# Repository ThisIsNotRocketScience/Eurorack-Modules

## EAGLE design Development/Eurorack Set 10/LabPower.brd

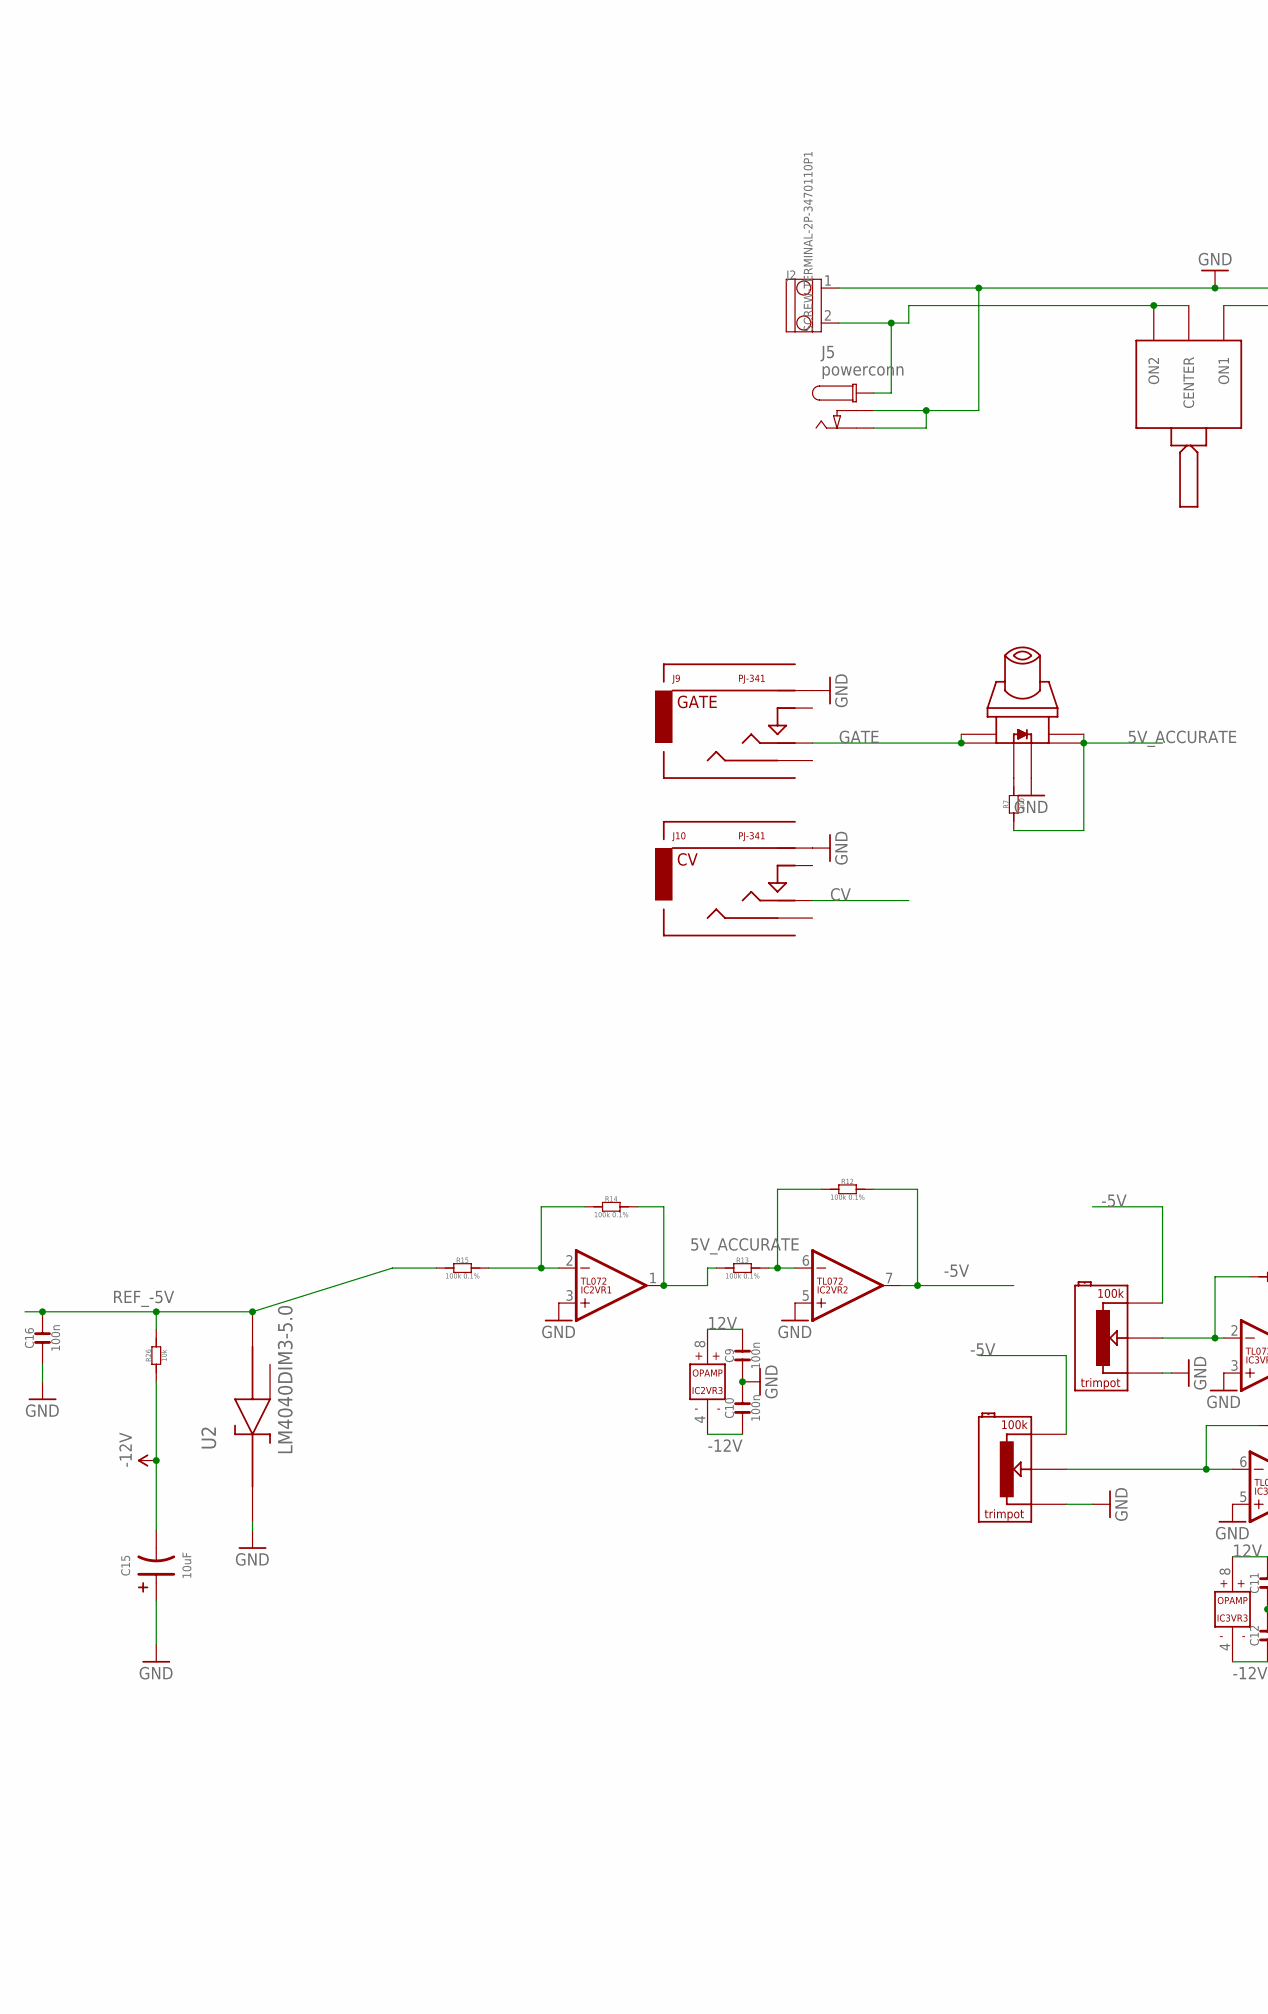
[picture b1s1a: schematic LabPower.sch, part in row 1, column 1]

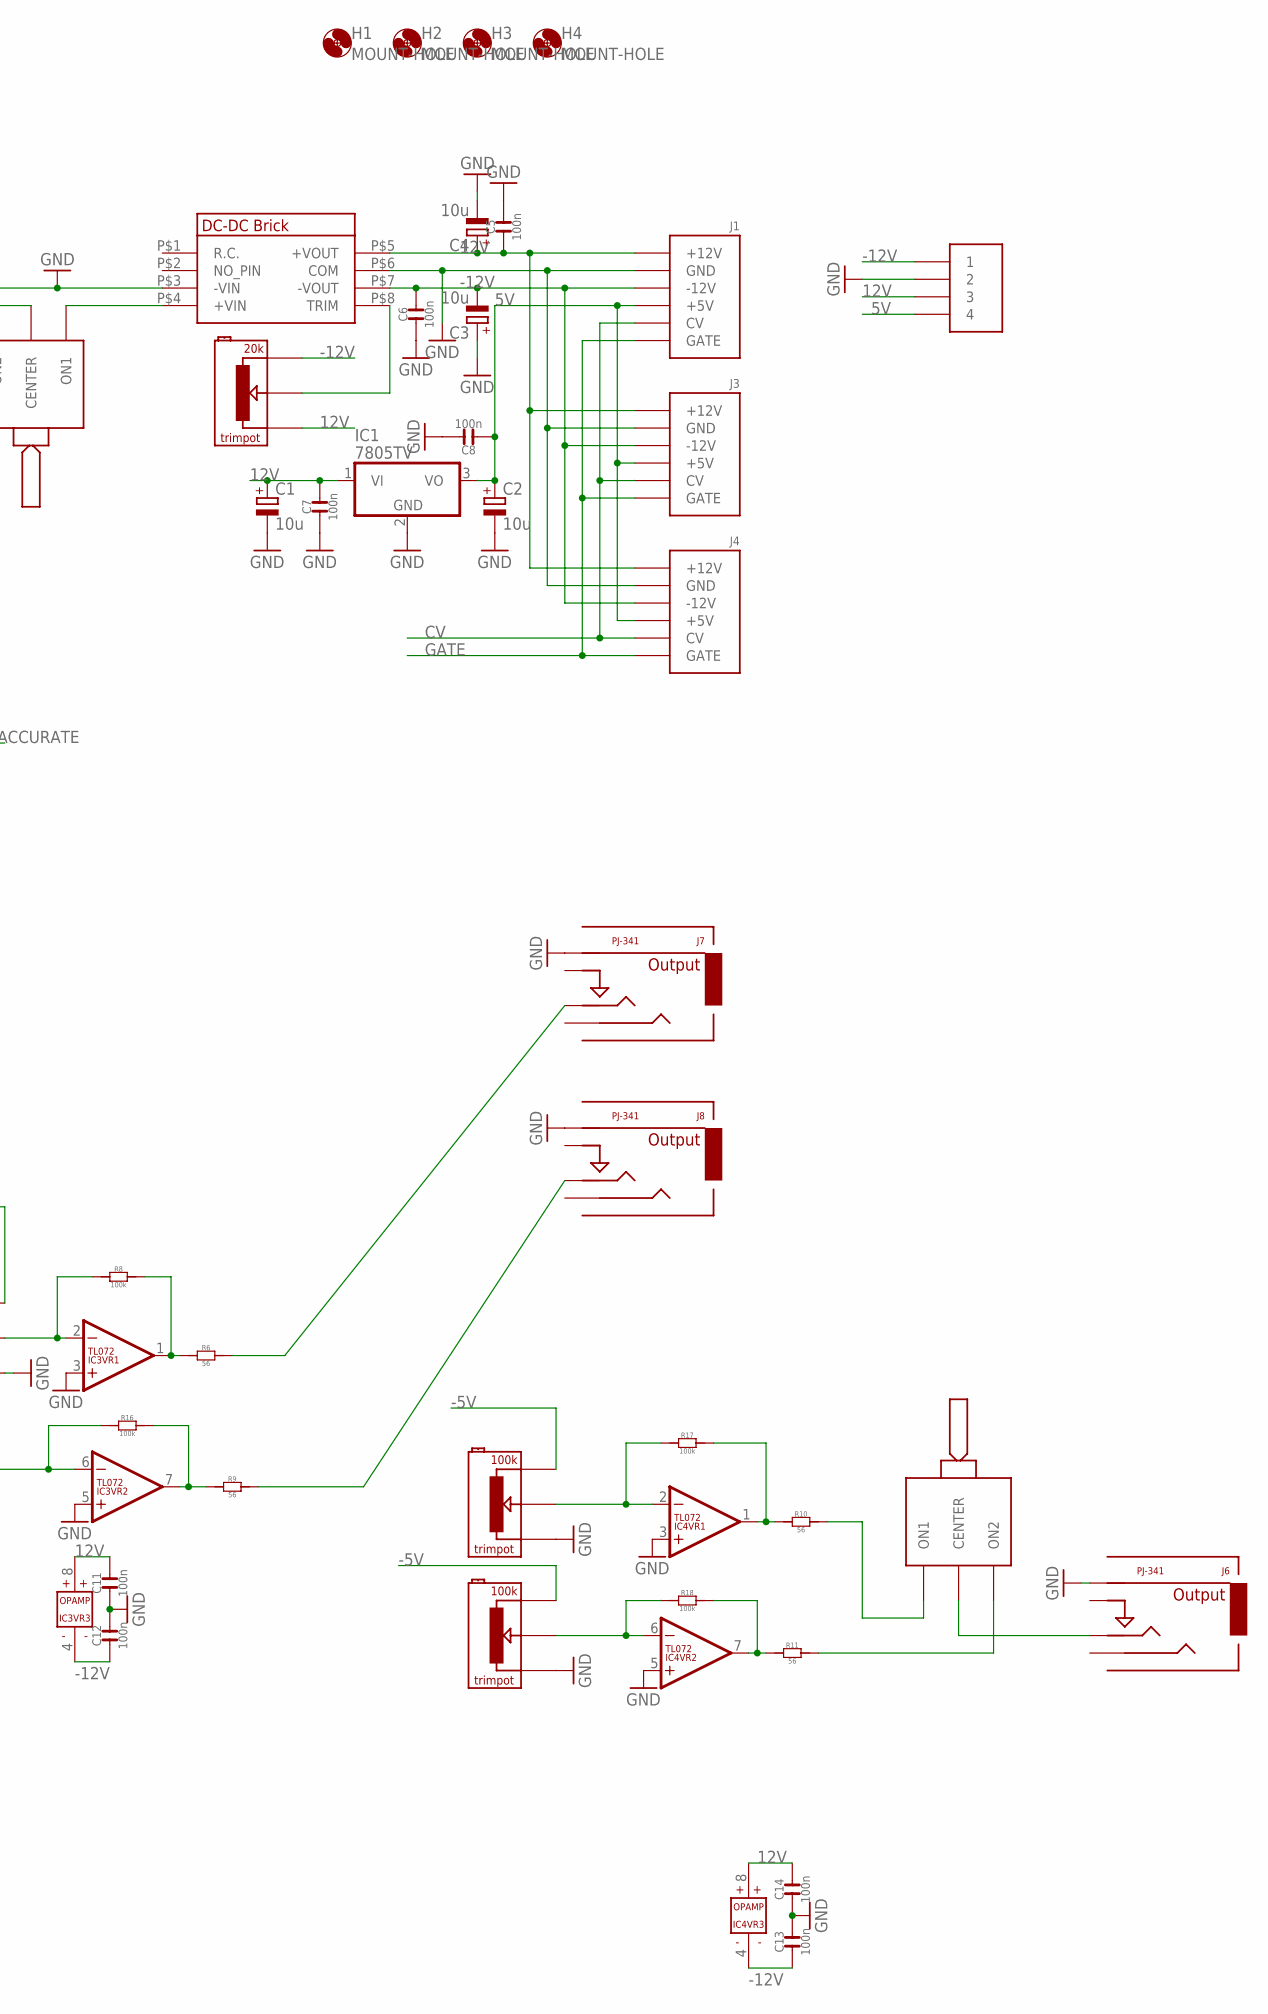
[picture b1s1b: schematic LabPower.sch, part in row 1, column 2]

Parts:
C1, C2, C3, C4: 10u; CASE_B
C5, C6, C7, C8, C9, C10, C11, C12, C13, C14: 100n; C0603
C15: 10uF; CASE-A_3216; MPN TAJB106K020RNJ
C16: 100n; C0603; MPN 06035C104KAT2A
H1, H2, H3, H4: MOUNT-HOLE; 3.2-NOMARKINGS-SMALLSAFEZONE
IC1: 7805TV; TO220V
IC2, IC3, IC4: TL072; SO08
J1: POWERSHROUDED; POWER_16_SHROUDED
J2: SCREW-TERMINAL-2P-3470110P1; 2P-5.0
J3, J4: POWER_SHROUDED_NOTEXT; POWER_16_SHROUDED_NOTEXT
J5: powerconn; DC_BARREL_JACK_PTH_2MM_2
J6, J7, J8: PJ-341; 3.5MM-JACK-SWITCH-13MM-OUTPUT
J9, J10: PJ-341; 3.5MM-JACK-SWITCH-13MM-INPUT
R1: 20k; TRIMPOT
R2, R3, R4, R5: 100k; TRIMPOT
R6, R9, R10, R11: 56; R0603
R7: 200; R0603
R8, R16, R17, R18: 100k; R0603
R12, R13, R14, R15: 100k 0.1%; R0603
R26: 10k; R0603
S1, S2: ONOFFON; MULTICOMP1MS-ONOFFON
S3: SWITCH_W_LED_PB6149L-X-102YELLOW; PB6149L
U2: LM4040DIM3-5.0; SOT95P237X112-3N
U$1: DKA30; MEANWELL_DKA30
U$2: 4PIN5MM

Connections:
5V: C2.+, C8.1, IC1.3 (VO), J1.11 (+5V), J1.12 (+5V), J3.11 (+5V), J3.12 (+5V), J4.11 (+5V), J4.12 (+5V), U$2.4
5V_ACCURATE: IC2.1 (OUT), R7.1, R13.1, R14.2, S3.3, S3.4
12V: C1.+, C4.+, C5.1, C7.2, C9.2, C11.2, C14.2, IC1.1 (VI), IC2.8 (V+), IC3.8 (V+), IC4.8 (V+), J1.9 (+12V), J1.10 (+12V), J3.9 (+12V), J3.10 (+12V), J4.9 (+12V), J4.10 (+12V), R1.P$1, U$1.P$5 (+VOUT), U$2.3
-5V: IC2.7 (OUT), R2.P$3, R3.P$3, R4.P$3, R5.P$3, R12.2
-12V: C3.-, C6.2, C10.1, C12.1, C13.1, C15.- (2), IC2.4 (V-), IC3.4 (V-), IC4.4 (V-), J1.1 (-12V), J1.2 (-12V), J3.1 (-12V), J3.2 (-12V), J4.1 (-12V), J4.2 (-12V), R1.P$3, R26.1, U$1.P$7 (-VOUT), U$2.1
CV: J1.13 (CV), J1.14 (CV), J3.13 (CV), J3.14 (CV), J4.13 (CV), J4.14 (CV), J10.TIP@3 (TIP)
GATE: J1.15 (GATE), J1.16 (GATE), J3.15 (GATE), J3.16 (GATE), J4.15 (GATE), J4.16 (GATE), J9.TIP@3 (TIP), S3.1, S3.2
GND: C1.-, C2.-, C3.+, C4.-, C5.2, C6.1, C7.1, C8.2, C9.1, C10.2, C11.1, C12.2, C13.2, C14.1, C15.+ (1), C16.1, IC1.2 (GND), IC2.3 (+IN), IC2.5 (+IN), IC3.3 (+IN), IC3.5 (+IN), IC4.3 (+IN), IC4.5 (+IN), J1.3 (GND), J1.4 (GND), J1.5 (GND), J1.6 (GND), J1.7 (GND), J1.8 (GND), J2.1, J3.3 (GND), J3.4 (GND), J3.5 (GND), J3.6 (GND), J3.7 (GND), J3.8 (GND), J4.3 (GND), J4.4 (GND), J4.5 (GND), J4.6 (GND), J4.7 (GND), J4.8 (GND), J5.P2 (P3), J5.P3 (P2), J6.RING@3 (RING), J7.RING@3 (RING), J8.RING@3 (RING), J9.RING@3 (RING), J10.RING@3 (RING), R2.P$1, R3.P$1, R4.P$1, R5.P$1, S3.LEDNEG (NEG), U2.1 (CATHODE), U$1.P$3 (-VIN), U$1.P$6 (COM), U$2.2
unnamed: R7.2, S3.LEDPOS (POS)
unnamed: J6.TIP@3 (TIP), S2.2 (CENTER)
unnamed: IC2.2 (-IN), R14.1, R15.2
unnamed: R1.P$2, U$1.P$8 (TRIM)
unnamed: S1.1 (ON1), U$1.P$4 (+VIN)
unnamed: IC2.6 (-IN), R12.1, R13.2
unnamed: IC3.6 (-IN), R4.P$2, R16.1
unnamed: IC3.1 (OUT), R6.1, R8.2
unnamed: IC3.7 (OUT), R9.1, R16.2
unnamed: J7.TIP@3 (TIP), R6.2
unnamed: J8.TIP@3 (TIP), R9.2
unnamed: IC3.2 (-IN), R3.P$2, R8.1
unnamed: IC4.1 (OUT), R10.1, R17.2
unnamed: R10.2, S2.1 (ON1)
unnamed: IC4.7 (OUT), R11.1, R18.2
unnamed: R11.2, S2.3 (ON2)
unnamed: IC4.2 (-IN), R5.P$2, R17.1
unnamed: IC4.6 (-IN), R2.P$2, R18.1
POSITIVE_INPUT: J2.2, J5.P1, S1.2 (CENTER), S1.3 (ON2)
REF_-5V: C16.2, R15.1, R26.2, U2.2 (ANODE)

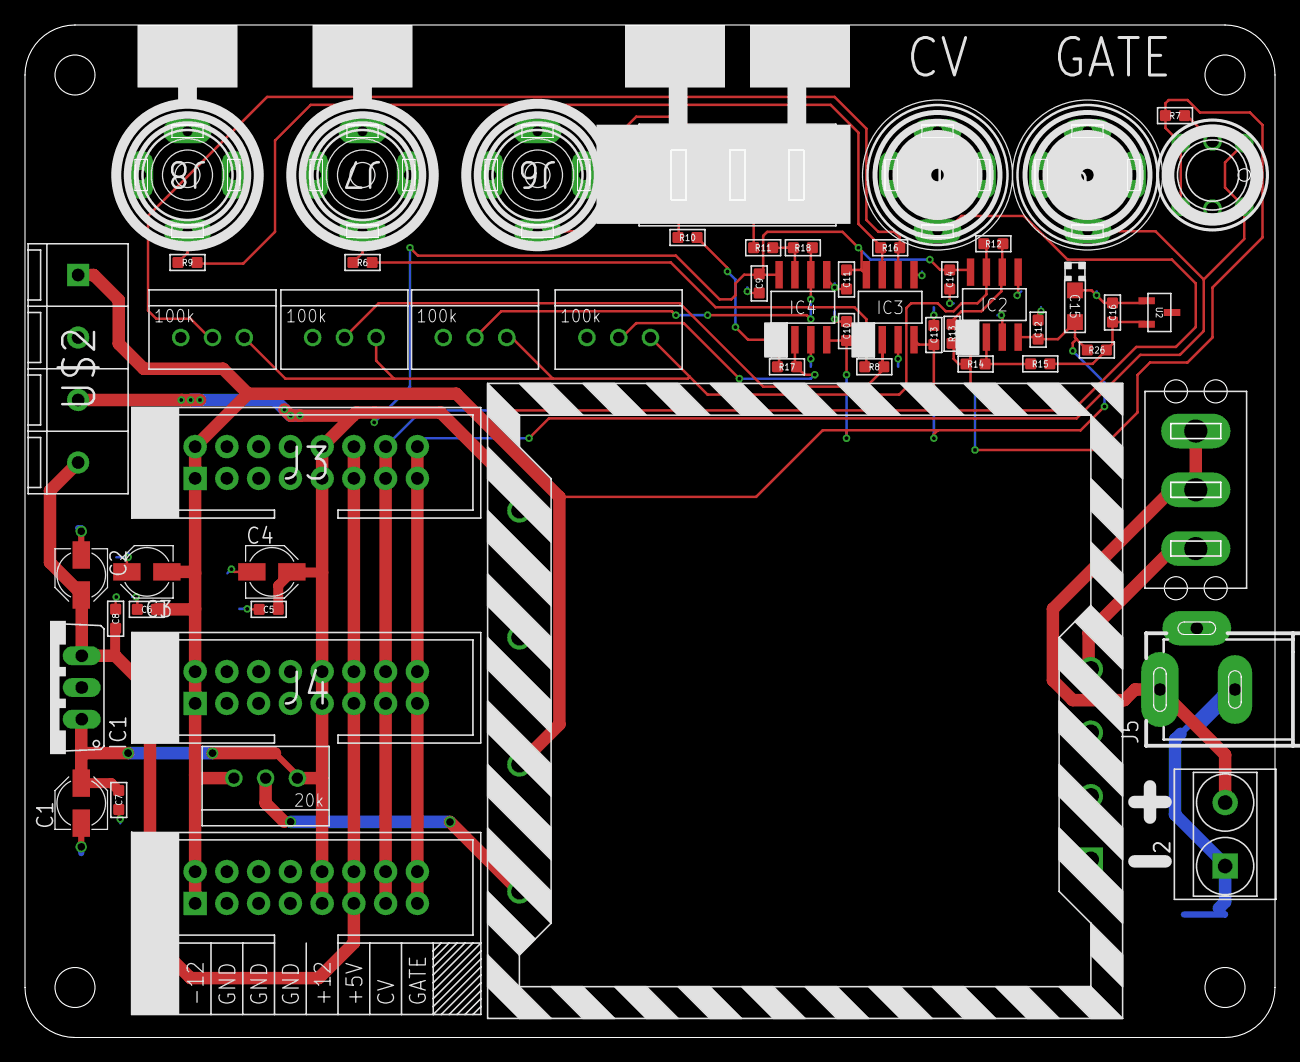
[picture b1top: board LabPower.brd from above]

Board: 2 copper layers, 100.0 x 81.0 mm, 59 parts (0 on the bottom side), 28 nets.

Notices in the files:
parts and their libraries:
SparkFun-Aesthetics: Licensing: CC v3.0 Share-Alike You are welcome to use this library for commercial purposes.
